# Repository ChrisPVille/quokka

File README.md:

# quokka
Quokka 6502 Microprocessor Trainer

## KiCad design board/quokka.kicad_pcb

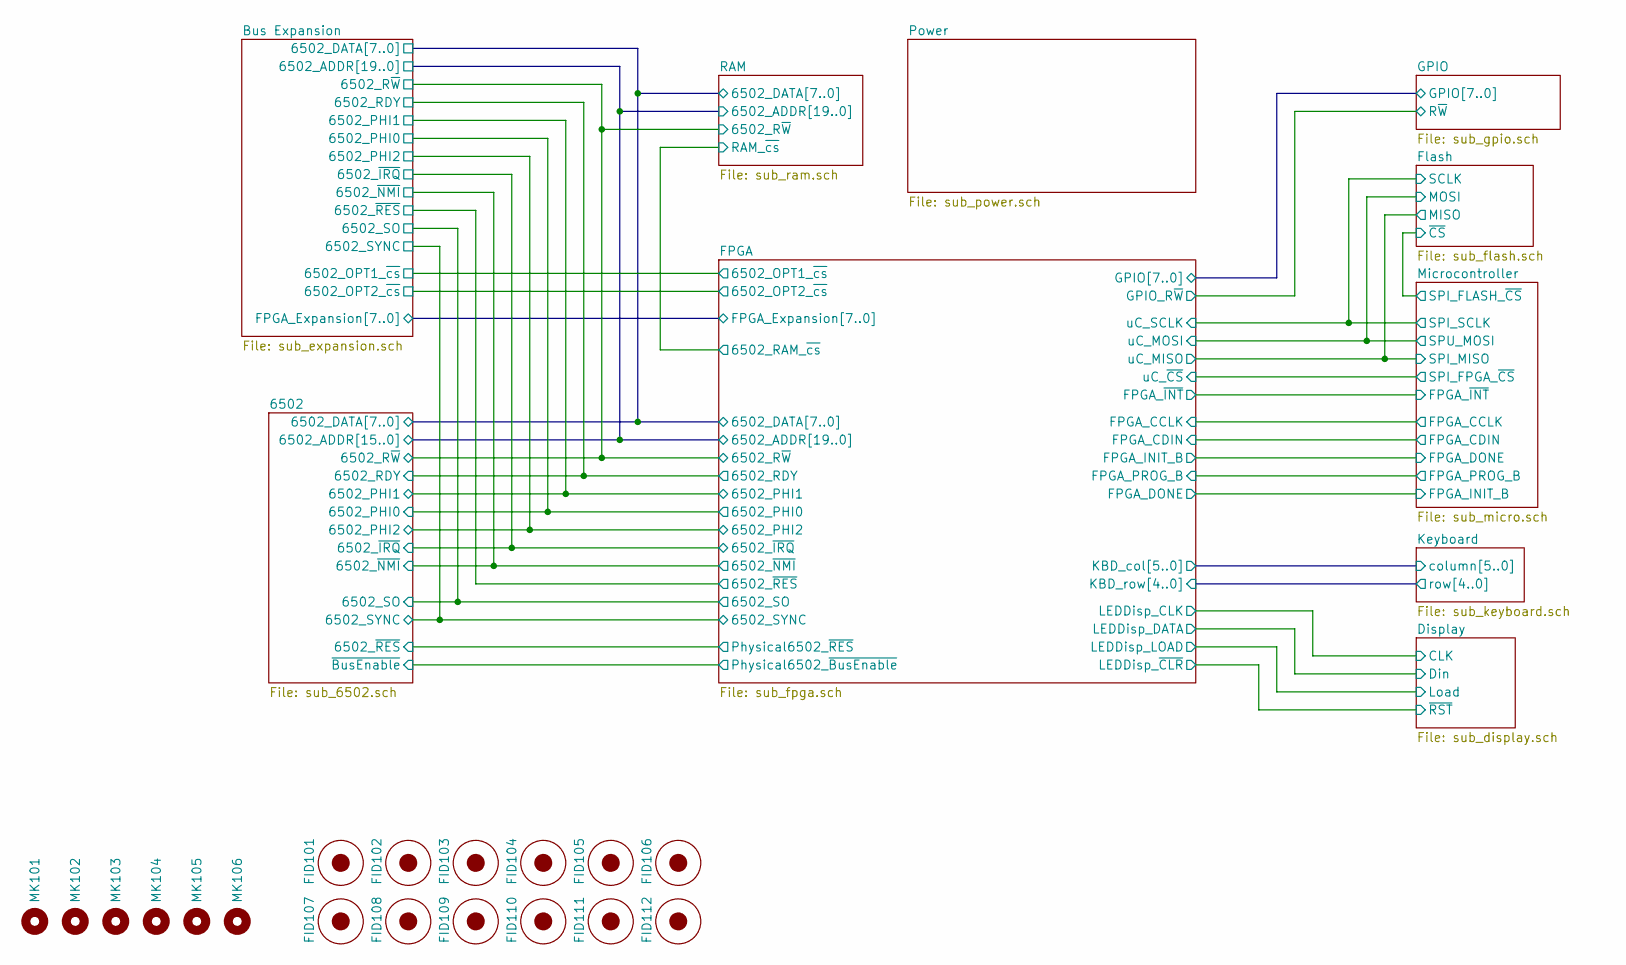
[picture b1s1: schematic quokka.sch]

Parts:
FID101, FID102, FID103, FID107, FID108, FID109, FID110, FID111, FID112: Fiducial; Fiducial_1mm_Dia_2.54mm_Outer_CopperTop
FID104, FID105, FID106: Fiducial; Fiducial_1mm_Dia_2.54mm_Outer_CopperBottom
MK101, MK102, MK103, MK104, MK105, MK106: Mounting_Hole; MountingHole_4.5mm

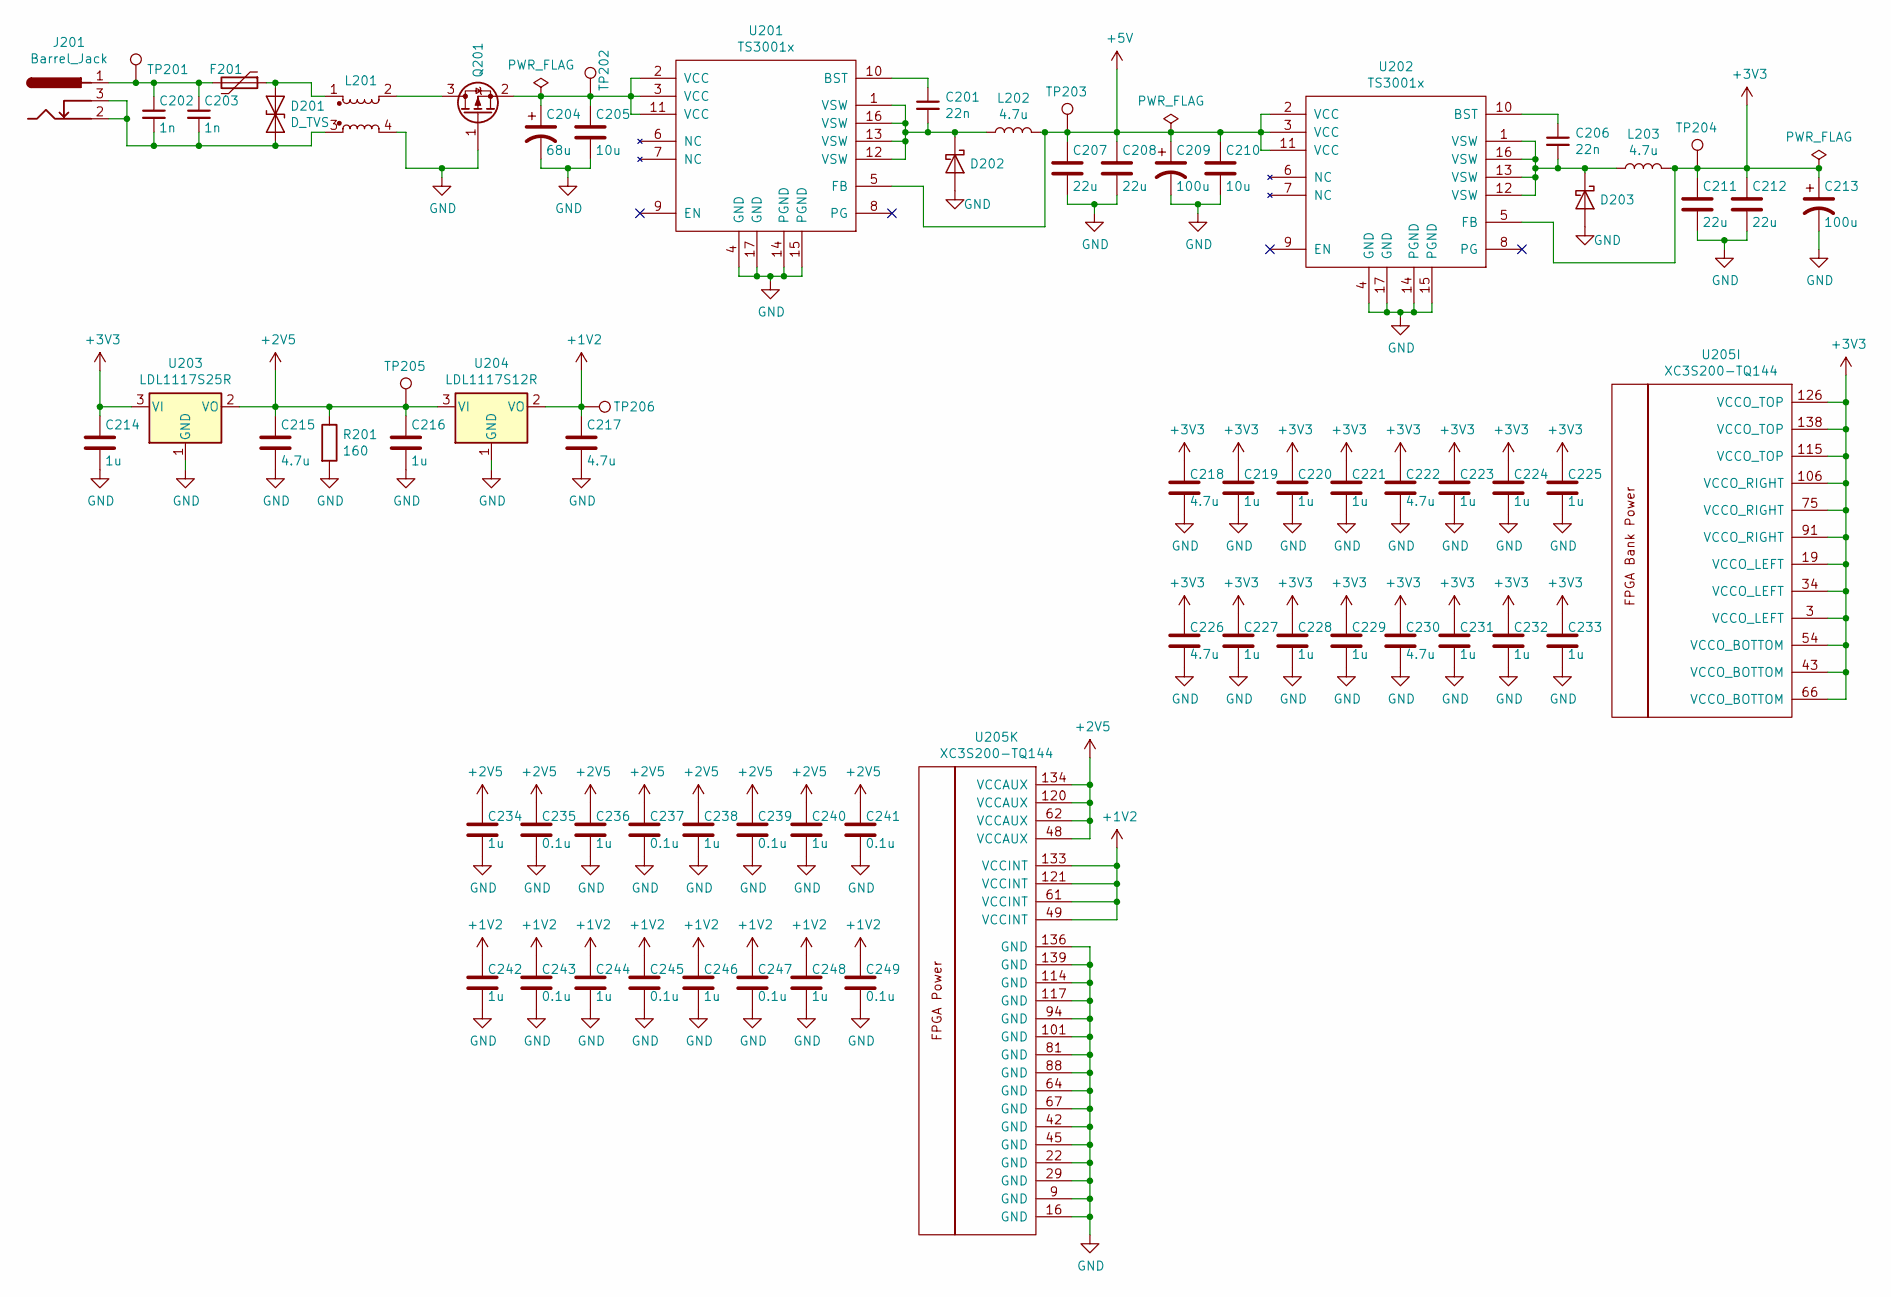
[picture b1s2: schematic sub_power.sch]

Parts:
C201, C206: 22n; C_0603_1608Metric
C202, C203: 1n; C_1206_3216Metric
C204: 68u; CP_Radial_D6.3mm_P2.50mm
C205, C210: 10u; C_1206_3216Metric
C207, C208, C211, C212: 22u; C_0805_2012Metric
C209, C213: 100u; CP_Radial_D8.0mm_P3.50mm
C214, C216, C219, C220, C221, C223, C224, C225, C227, C228, C229, C231, C232, C233, C234, C236, C238, C240, C242, C244, C246, C248: 1u; C_0603_1608Metric
C215, C217, C218, C222, C226, C230: 4.7u; C_0603_1608Metric
C235, C237, C239, C241, C243, C245, C247, C249: 0.1u; C_0603_1608Metric
D201: D_TVS; D_SMA
D202, D203: D_Schottky; D_SOD-123F
F201: Polyfuse; Fuse_2920_7451Metric
J201: Barrel_Jack; BarrelJack_CUI_PJ-102AH_Horizontal
L201: Power Choke; CM2021Y330R-10
L202, L203: 4.7u; L_Taiyo-Yuden_NR-60xx
Q201: Q_PMOS_GSD; SOT-23
R201: 160; R_1206_3216Metric
TP201, TP202, TP203, TP204, TP205, TP206: Test_Point; TestPoint_Pad_D1.5mm
U201, U202: TS3001x; UQFN-16-1EP_3x3mm_P0.5mm_EP1.75x1.75mm
U203: LDL1117S25R; SOT-223-3_TabPin2
U204: LDL1117S12R; SOT-223-3_TabPin2
U205: XC3S200-TQ144; LQFP-144_20x20mm_P0.5mm

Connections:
+1V2: C217.1, C242.1, C243.1, C244.1, C245.1, C246.1, C247.1, C248.1, C249.1, TP206.1, U204.2 (VO), U205.49 (VCCINT), U205.61 (VCCINT), U205.121 (VCCINT), U205.133 (VCCINT)
+2V5: C215.1, C216.1, C234.1, C235.1, C236.1, C237.1, C238.1, C239.1, C240.1, C241.1, R201.1, TP205.1, U203.2 (VO), U204.3 (VI), U205.48 (VCCAUX), U205.62 (VCCAUX), U205.120 (VCCAUX), U205.134 (VCCAUX); also elsewhere on the board
+5V: C207.1, C208.1, C209.1, C210.1, L202.2, TP203.1, U201.5 (FB), U202.2 (VCC), U202.3 (VCC), U202.11 (VCC); also elsewhere on the board
GND: C204.2, C205.2, C207.2, C208.2, C209.2, C210.2, C211.2, C212.2, C213.2, C214.2, C215.2, C216.2, C217.2, C218.2, C219.2, C220.2, C221.2, C222.2, C223.2, C224.2, C225.2, C226.2, C227.2, C228.2, C229.2, C230.2, C231.2, C232.2, C233.2, C234.2, C235.2, C236.2, C237.2, C238.2, C239.2, C240.2, C241.2, C242.2, C243.2, C244.2, C245.2, C246.2, C247.2, C248.2, C249.2, D202.2 (A), D203.2 (A), L201.4, Q201.1 (G), R201.2, U201.4 (GND), U201.14 (PGND), U201.15 (PGND), U201.17 (GND), U202.4 (GND), U202.14 (PGND), U202.15 (PGND), U202.17 (GND), U203.1 (GND), U204.1 (GND), U205.9 (GND), U205.16 (GND), U205.22 (GND), U205.29 (GND), U205.42 (GND), U205.45 (GND), U205.64 (GND), U205.67 (GND), U205.81 (GND), U205.88 (GND), U205.94 (GND), U205.101 (GND), U205.114 (GND), U205.117 (GND), U205.136 (GND), U205.139 (GND); also elsewhere on the board
unnamed: C201.1, U201.10 (BST)
unnamed: C201.2, D202.1 (K), L202.1, U201.1 (VSW), U201.12 (VSW), U201.13 (VSW), U201.16 (VSW)
unnamed: C202.1, C203.1, F201.2, J201.1, TP201.1
unnamed: C202.2, C203.2, D201.2 (A2), J201.2, J201.3, L201.3
unnamed: C204.1, C205.1, Q201.2 (S), TP202.1, U201.2 (VCC), U201.3 (VCC), U201.11 (VCC)
unnamed: C206.1, U202.10 (BST)
unnamed: C206.2, D203.1 (K), L203.1, U202.1 (VSW), U202.12 (VSW), U202.13 (VSW), U202.16 (VSW)
unnamed: D201.1 (A1), F201.1, L201.1
unnamed: L201.2, Q201.3 (D)

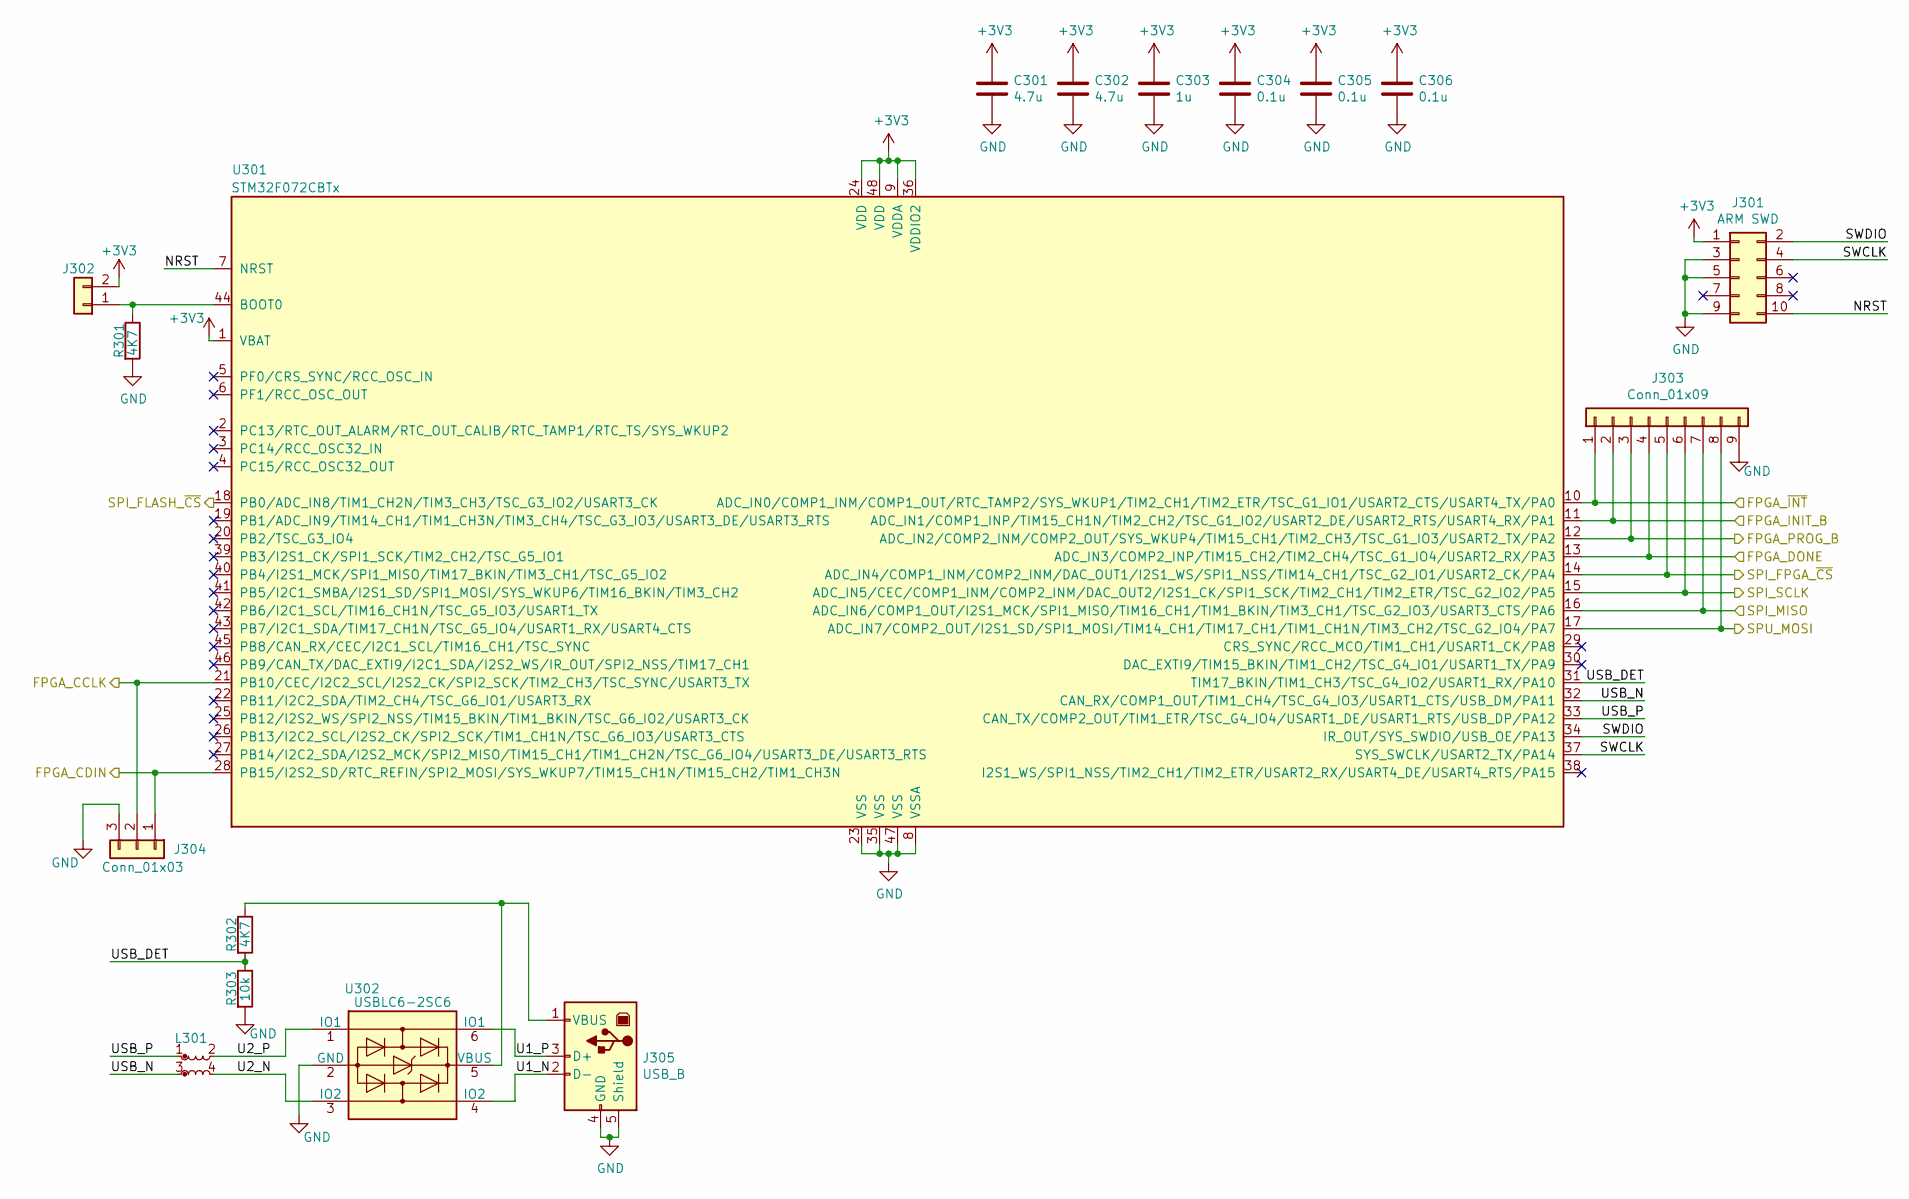
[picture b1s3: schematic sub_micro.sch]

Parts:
C301, C302: 4.7u; C_0603_1608Metric
C303: 1u; C_0603_1608Metric
C304, C305, C306: 0.1u; C_0603_1608Metric
J301: ARM SWD; PinHeader_2x05_P1.27mm_Vertical_SMD
J302: Conn_01x02; PinHeader_1x02_P2.54mm_Vertical
J303: Conn_01x09; PinHeader_1x09_P2.54mm_Vertical
J304: Conn_01x03; PinHeader_1x03_P2.54mm_Vertical
J305: USB_B; UE27BCX4
L301: USB Choke; DLW21H
R301, R302: 4K7; R_0603_1608Metric
R303: 10k; R_0603_1608Metric
U301: STM32F072CBTx; LQFP-48_7x7mm_P0.5mm
U302: USBLC6-2SC6; SOT-23-6

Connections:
/FPGA/FPGA_CCLK: J304.2, U301.21 (PB10/CEC/I2C2_SCL/I2S2_CK/SPI2_SCK/TIM2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); also elsewhere on the board
/FPGA/FPGA_CDIN: J304.1, U301.28 (PB15/I2S2_SD/RTC_REFIN/SPI2_MOSI/SYS_WK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); also elsewhere on the board
/FPGA/FPGA_DONE: J303.2, U301.11 (ADC_IN1/COMP1_INP/TIM15_CH1N/TIM2_CH2/T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); also elsewhere on the board
/FPGA/FPGA_PROG_B: J303.3, U301.12 (ADC_IN2/COMP2_INM/COMP2_OUT/SYS_WKUP4/T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); also elsewhere on the board
/FPGA/FPGA_~INT: J303.1, U301.10 (ADC_IN0/COMP1_INM/COMP1_OUT/RTC_TAMP2/S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); also elsewhere on the board
/Flash/MISO: J303.7, U301.16 (ADC_IN6/COMP1_OUT/I2S1_MCK/SPI1_MISO/TI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); also elsewhere on the board
/Flash/MOSI: J303.8, U301.17 (ADC_IN7/COMP2_OUT/I2S1_SD/SPI1_MOSI/TIM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); also elsewhere on the board
/Flash/SCLK: J303.6, U301.15 (ADC_IN5/CEC/COMP1_INM/COMP2_INM/DAC_OUT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); also elsewhere on the board
/Microcontroller/FPGA_DONE: J303.4, U301.13 (ADC_IN3/COMP2_INP/TIM15_CH2/TIM2_CH4/TS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); also elsewhere on the board
/Microcontroller/NRST: J301.10, U301.7 (NRST)
/Microcontroller/SPI_FLASH_~CS: U301.18 (PB0/ADC_IN8/TIM1_CH2N/TIM3_CH3/TSC_G3_I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); also elsewhere on the board
/Microcontroller/SPI_FPGA_~CS: J303.5, U301.14 (ADC_IN4/COMP1_INM/COMP2_INM/DAC_OUT1/I2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); also elsewhere on the board
/Microcontroller/SWCLK: J301.4, U301.37 (SYS_SWCLK/USART2_TX/PA14)
/Microcontroller/SWDIO: J301.2, U301.34 (IR_OUT/SYS_SWDIO/USB_OE/PA13)
/Microcontroller/U1_N: J305.2 (D-), U302.4 (IO2)
/Microcontroller/U1_P: J305.3 (D+), U302.6 (IO1)
/Microcontroller/U2_N: L301.4, U302.3 (IO2)
/Microcontroller/U2_P: L301.2, U302.1 (IO1)
/Microcontroller/USB_DET: R302.2, R303.1, U301.31 (TIM17_BKIN/TIM1_CH3/TSC_G4_IO2/USART1_R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)
/Microcontroller/USB_N: L301.3, U301.32 (CAN_RX/COMP1_OUT/TIM1_CH4/TSC_G4_IO3/US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)
/Microcontroller/USB_P: L301.1, U301.33 (CAN_TX/COMP2_OUT/TIM1_ETR/TSC_G4_IO4/US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)
GND: C301.2, C302.2, C303.2, C304.2, C305.2, C306.2, J301.3, J301.5, J301.9, J303.9, J304.3, J305.4 (GND), J305.5 (Shield), R301.2, R303.2, U301.8 (VSSA), U301.23 (VSS), U301.35 (VSS), U301.47 (VSS), U302.2 (GND); also elsewhere on the board
unnamed: J302.1, R301.1, U301.44 (BOOT0)
unnamed: J305.1 (VBUS), R302.1, U302.5 (VBUS)

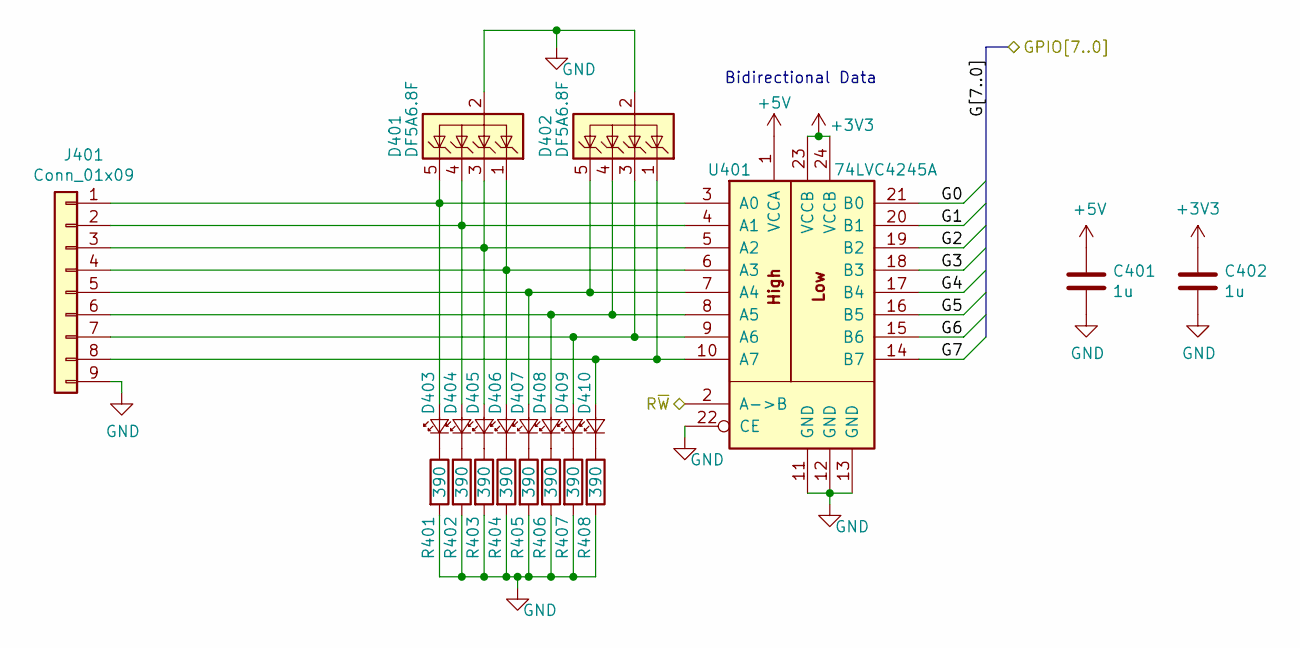
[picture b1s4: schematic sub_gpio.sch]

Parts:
C401, C402: 1u; C_0603_1608Metric
D401, D402: DF5A6.8F; SOT-353_SC-70-5
D403, D404, D405, D406, D407, D408, D409, D410: LED_Small; LED_0805_2012Metric
J401: Conn_01x09; PinHeader_1x09_P2.54mm_Vertical
R401, R402, R403, R404, R405, R406, R407, R408: 390; R_0603_1608Metric
U401: 74LVC4245A; TSSOP-24_4.4x7.8mm_P0.65mm

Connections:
+5V: C401.1, U401.1 (VCCA); also elsewhere on the board
/FPGA/G0: U401.21 (B0); also elsewhere on the board
/FPGA/G1: U401.20 (B1); also elsewhere on the board
/FPGA/G2: U401.19 (B2); also elsewhere on the board
/FPGA/G3: U401.18 (B3); also elsewhere on the board
/FPGA/G4: U401.17 (B4); also elsewhere on the board
/FPGA/G5: U401.16 (B5); also elsewhere on the board
/FPGA/G6: U401.15 (B6); also elsewhere on the board
/FPGA/G7: U401.14 (B7); also elsewhere on the board
/FPGA/GPIO_R~W: U401.2 (A->B); also elsewhere on the board
GND: C401.2, C402.2, D401.2 (A), D402.2 (A), J401.9, R401.2, R402.2, R403.2, R404.2, R405.2, R406.2, R407.2, R408.2, U401.11 (GND), U401.12 (GND), U401.13 (GND), U401.22 (CE); also elsewhere on the board
unnamed: D401.1 (K), D406.2 (A), J401.4, U401.6 (A3)
unnamed: D401.3 (K), D405.2 (A), J401.3, U401.5 (A2)
unnamed: D401.4 (K), D404.2 (A), J401.2, U401.4 (A1)
unnamed: D401.5 (K), D403.2 (A), J401.1, U401.3 (A0)
unnamed: D402.1 (K), D410.2 (A), J401.8, U401.10 (A7)
unnamed: D402.3 (K), D409.2 (A), J401.7, U401.9 (A6)
unnamed: D402.4 (K), D408.2 (A), J401.6, U401.8 (A5)
unnamed: D402.5 (K), D407.2 (A), J401.5, U401.7 (A4)
unnamed: D403.1 (K), R401.1
unnamed: D404.1 (K), R402.1
unnamed: D405.1 (K), R403.1
unnamed: D406.1 (K), R404.1
unnamed: D407.1 (K), R405.1
unnamed: D408.1 (K), R406.1
unnamed: D409.1 (K), R407.1
unnamed: D410.1 (K), R408.1

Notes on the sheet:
Bidirectional Data

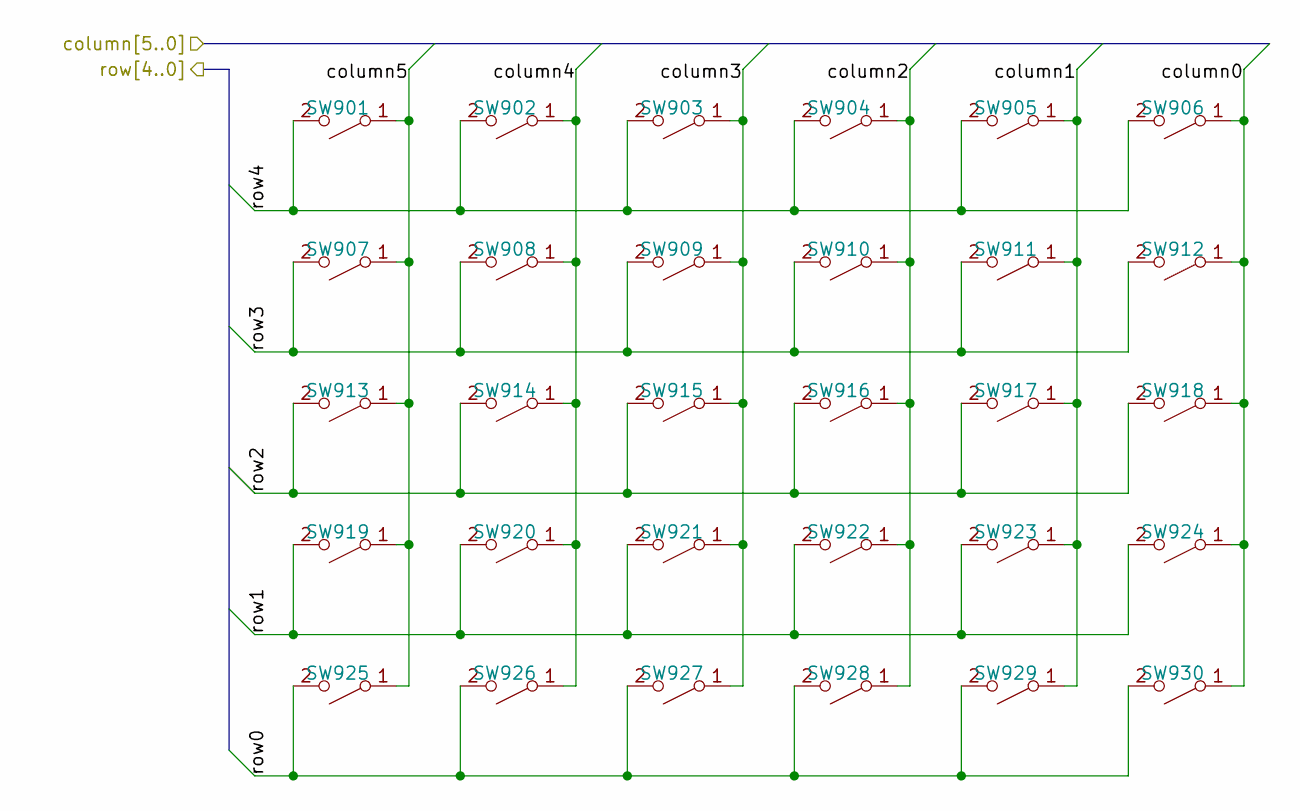
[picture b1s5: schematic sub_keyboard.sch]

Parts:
SW901, SW902, SW903, SW904, SW905, SW906, SW907, SW908, SW909, SW910, SW911, SW912, SW913, SW914, SW915, SW916, SW917, SW918, SW919, SW920, SW921, SW922, SW923, SW924, SW925, SW926, SW927, SW928, SW929, SW930: SW_SPST; SW_Cherry_MX1A_1.00u_PCB

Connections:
/FPGA/C0: SW906.1 (A), SW912.1 (A), SW918.1 (A), SW924.1 (A), SW930.1 (A); also elsewhere on the board
/FPGA/C1: SW905.1 (A), SW911.1 (A), SW917.1 (A), SW923.1 (A), SW929.1 (A); also elsewhere on the board
/FPGA/C2: SW904.1 (A), SW910.1 (A), SW916.1 (A), SW922.1 (A), SW928.1 (A); also elsewhere on the board
/FPGA/C3: SW903.1 (A), SW909.1 (A), SW915.1 (A), SW921.1 (A), SW927.1 (A); also elsewhere on the board
/FPGA/C4: SW902.1 (A), SW908.1 (A), SW914.1 (A), SW920.1 (A), SW926.1 (A); also elsewhere on the board
/FPGA/C5: SW901.1 (A), SW907.1 (A), SW913.1 (A), SW919.1 (A), SW925.1 (A); also elsewhere on the board
/FPGA/R0: SW925.2 (B), SW926.2 (B), SW927.2 (B), SW928.2 (B), SW929.2 (B), SW930.2 (B); also elsewhere on the board
/FPGA/R1: SW919.2 (B), SW920.2 (B), SW921.2 (B), SW922.2 (B), SW923.2 (B), SW924.2 (B); also elsewhere on the board
/FPGA/R2: SW913.2 (B), SW914.2 (B), SW915.2 (B), SW916.2 (B), SW917.2 (B), SW918.2 (B); also elsewhere on the board
/FPGA/R3: SW907.2 (B), SW908.2 (B), SW909.2 (B), SW910.2 (B), SW911.2 (B), SW912.2 (B); also elsewhere on the board
/FPGA/R4: SW901.2 (B), SW902.2 (B), SW903.2 (B), SW904.2 (B), SW905.2 (B), SW906.2 (B); also elsewhere on the board

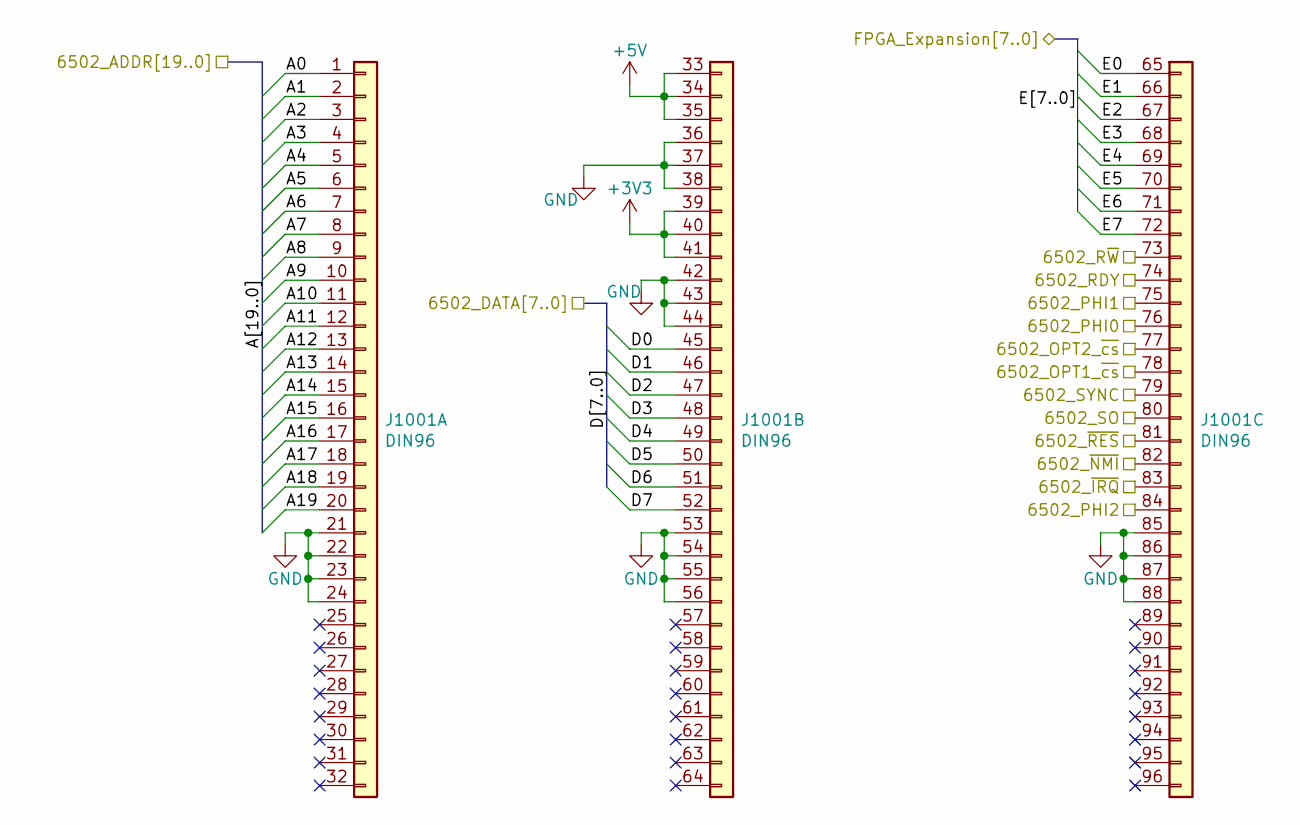
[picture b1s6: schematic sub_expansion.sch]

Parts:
J1001: DIN96; DIN-8609-2030

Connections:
+5V: J1001.33 (Pin_1), J1001.34 (Pin_2), J1001.35 (Pin_3); also elsewhere on the board
/6502/6502_PHI0: J1001.76 (Pin_12); also elsewhere on the board
/6502/6502_PHI1: J1001.75 (Pin_11); also elsewhere on the board
/6502/6502_PHI2: J1001.84 (Pin_20); also elsewhere on the board
/6502/6502_RDY: J1001.74 (Pin_10); also elsewhere on the board
/6502/6502_R~W: J1001.73 (Pin_9); also elsewhere on the board
/6502/6502_SO: J1001.80 (Pin_16); also elsewhere on the board
/6502/6502_SYNC: J1001.79 (Pin_15); also elsewhere on the board
/6502/6502_~IRQ: J1001.83 (Pin_19); also elsewhere on the board
/6502/6502_~NMI: J1001.82 (Pin_18); also elsewhere on the board
/6502/B_D0: J1001.45 (Pin_13); also elsewhere on the board
/6502/B_D1: J1001.46 (Pin_14); also elsewhere on the board
/6502/B_D2: J1001.47 (Pin_15); also elsewhere on the board
/6502/B_D3: J1001.48 (Pin_16); also elsewhere on the board
/6502/B_D4: J1001.49 (Pin_17); also elsewhere on the board
/6502/B_D5: J1001.50 (Pin_18); also elsewhere on the board
/6502/B_D6: J1001.51 (Pin_19); also elsewhere on the board
/6502/B_D7: J1001.52 (Pin_20); also elsewhere on the board
/Bus Expansion/6502_OPT1_~cs: J1001.78 (Pin_14); also elsewhere on the board
/Bus Expansion/6502_OPT2_~cs: J1001.77 (Pin_13); also elsewhere on the board
/Bus Expansion/6502_~RES: J1001.81 (Pin_17); also elsewhere on the board
/Bus Expansion/A0: J1001.1; also elsewhere on the board
/Bus Expansion/A1: J1001.2; also elsewhere on the board
/Bus Expansion/A2: J1001.3; also elsewhere on the board
/Bus Expansion/A3: J1001.4; also elsewhere on the board
/Bus Expansion/A4: J1001.5; also elsewhere on the board
/Bus Expansion/A5: J1001.6; also elsewhere on the board
/Bus Expansion/A6: J1001.7; also elsewhere on the board
/Bus Expansion/A7: J1001.8; also elsewhere on the board
/Bus Expansion/A8: J1001.9; also elsewhere on the board
/Bus Expansion/A9: J1001.10; also elsewhere on the board
/Bus Expansion/A10: J1001.11; also elsewhere on the board
/Bus Expansion/A11: J1001.12; also elsewhere on the board
/Bus Expansion/A12: J1001.13; also elsewhere on the board
/Bus Expansion/A13: J1001.14; also elsewhere on the board
/Bus Expansion/A14: J1001.15; also elsewhere on the board
/Bus Expansion/A15: J1001.16; also elsewhere on the board
/Bus Expansion/A16: J1001.17; also elsewhere on the board
/Bus Expansion/A17: J1001.18; also elsewhere on the board
/Bus Expansion/A18: J1001.19; also elsewhere on the board
/Bus Expansion/A19: J1001.20; also elsewhere on the board
/Bus Expansion/E0: J1001.65 (Pin_1); also elsewhere on the board
/Bus Expansion/E1: J1001.66 (Pin_2); also elsewhere on the board
/Bus Expansion/E2: J1001.67 (Pin_3); also elsewhere on the board
/Bus Expansion/E3: J1001.68 (Pin_4); also elsewhere on the board
/Bus Expansion/E4: J1001.69 (Pin_5); also elsewhere on the board
/Bus Expansion/E5: J1001.70 (Pin_6); also elsewhere on the board
/Bus Expansion/E6: J1001.71 (Pin_7); also elsewhere on the board
/Bus Expansion/E7: J1001.72 (Pin_8); also elsewhere on the board
GND: J1001.21, J1001.22, J1001.23, J1001.24, J1001.36 (Pin_4), J1001.37 (Pin_5), J1001.38 (Pin_6), J1001.42 (Pin_10), J1001.43 (Pin_11), J1001.44 (Pin_12), J1001.53 (Pin_21), J1001.54 (Pin_22), J1001.55 (Pin_23), J1001.56 (Pin_24), J1001.85 (Pin_21), J1001.86 (Pin_22), J1001.87 (Pin_23), J1001.88 (Pin_24); also elsewhere on the board

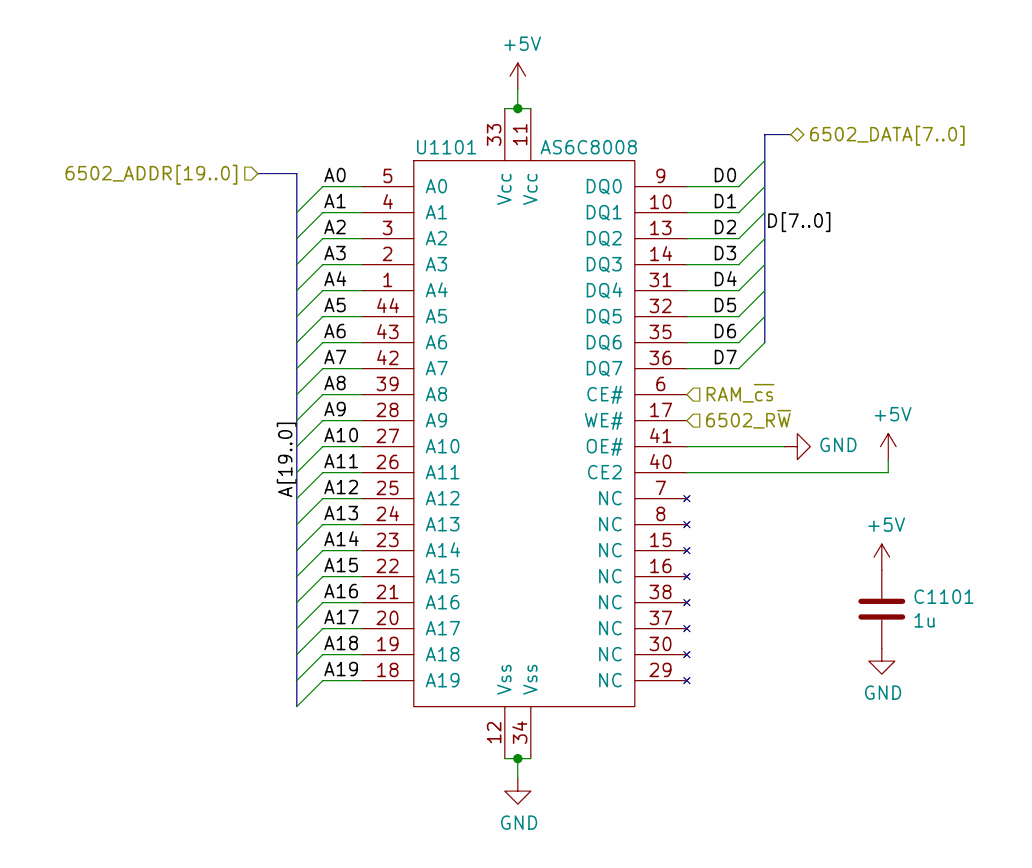
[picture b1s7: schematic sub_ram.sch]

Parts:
C1101: 1u; C_0603_1608Metric
U1101: AS6C8008; AS6C8008-SOIC-44

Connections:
+5V: C1101.1, U1101.11 (Vcc), U1101.33 (Vcc), U1101.40 (CE2); also elsewhere on the board
/6502/6502_R~W: U1101.17 (WE#); also elsewhere on the board
/6502/B_D0: U1101.9 (DQ0); also elsewhere on the board
/6502/B_D1: U1101.10 (DQ1); also elsewhere on the board
/6502/B_D2: U1101.13 (DQ2); also elsewhere on the board
/6502/B_D3: U1101.14 (DQ3); also elsewhere on the board
/6502/B_D4: U1101.31 (DQ4); also elsewhere on the board
/6502/B_D5: U1101.32 (DQ5); also elsewhere on the board
/6502/B_D6: U1101.35 (DQ6); also elsewhere on the board
/6502/B_D7: U1101.36 (DQ7); also elsewhere on the board
/Bus Expansion/A0: U1101.5 (A0); also elsewhere on the board
/Bus Expansion/A1: U1101.4 (A1); also elsewhere on the board
/Bus Expansion/A2: U1101.3 (A2); also elsewhere on the board
/Bus Expansion/A3: U1101.2 (A3); also elsewhere on the board
/Bus Expansion/A4: U1101.1 (A4); also elsewhere on the board
/Bus Expansion/A5: U1101.44 (A5); also elsewhere on the board
/Bus Expansion/A6: U1101.43 (A6); also elsewhere on the board
/Bus Expansion/A7: U1101.42 (A7); also elsewhere on the board
/Bus Expansion/A8: U1101.39 (A8); also elsewhere on the board
/Bus Expansion/A9: U1101.28 (A9); also elsewhere on the board
/Bus Expansion/A10: U1101.27 (A10); also elsewhere on the board
/Bus Expansion/A11: U1101.26 (A11); also elsewhere on the board
/Bus Expansion/A12: U1101.25 (A12); also elsewhere on the board
/Bus Expansion/A13: U1101.24 (A13); also elsewhere on the board
/Bus Expansion/A14: U1101.23 (A14); also elsewhere on the board
/Bus Expansion/A15: U1101.22 (A15); also elsewhere on the board
/Bus Expansion/A16: U1101.21 (A16); also elsewhere on the board
/Bus Expansion/A17: U1101.20 (A17); also elsewhere on the board
/Bus Expansion/A18: U1101.19 (A18); also elsewhere on the board
/Bus Expansion/A19: U1101.18 (A19); also elsewhere on the board
/FPGA/6502_RAM_~cs: U1101.6 (CE#); also elsewhere on the board
GND: C1101.2, U1101.12 (Vss), U1101.34 (Vss), U1101.41 (OE#); also elsewhere on the board

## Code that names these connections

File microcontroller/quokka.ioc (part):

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Mcu.Name=STM32F072C(8-B)Tx
Mcu.Package=LQFP48
Mcu.UserName=STM32F072CBTx
PA0.Signal=GPIO_Input
PA1.Signal=GPIO_Input
PA11.Mode=Device
PA11.Signal=USB_DM
PA12.Mode=Device
PA12.Signal=USB_DP
PA13.Mode=Serial_Wire
PA13.Signal=SYS_SWDIO
PA14.Mode=Serial_Wire
PA14.Signal=SYS_SWCLK
PA2.Signal=GPIO_Output
PA3.Signal=GPIO_Input
PA4.Mode=NSS_Signal_Hard_Output
PA4.Signal=SPI1_NSS
PA5.Mode=Full_Duplex_Master
PA5.Signal=SPI1_SCK
PA6.Mode=Full_Duplex_Master
PA6.Signal=SPI1_MISO
PA7.Mode=Full_Duplex_Master
PA7.Signal=SPI1_MOSI
PB0.Signal=GPIO_Output
PB10.GPIOParameters=GPIO_PuPd
PB10.GPIO_PuPd=GPIO_NOPULL
PB10.Mode=TX_Only_Simplex_Unidirect_Master
PB10.Signal=SPI2_SCK
PB15.Mode=TX_Only_Simplex_Unidirect_Master
PB15.Signal=SPI2_MOSI
RCC.SYSCLKFreq_VALUE=48000000
RCC.SYSCLKSource=RCC_SYSCLKSOURCE_HSI48

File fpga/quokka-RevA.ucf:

NET "RAW25MHZ" LOC = P53 | IOSTANDARD = LVCMOS33 | TNM_NET = "RAW25MHZ";
TIMESPEC TS_RAW25MHZ = PERIOD "RAW25MHZ" 25 MHz HIGH 50 % INPUT_JITTER 5 ps;

NET "G[7]" LOC = P52 | IOSTANDARD = LVCMOS33;
NET "G[6]" LOC = P51 | IOSTANDARD = LVCMOS33;
NET "G[5]" LOC = P50 | IOSTANDARD = LVCMOS33;
NET "G[4]" LOC = P47 | IOSTANDARD = LVCMOS33;
NET "G[3]" LOC = P46 | IOSTANDARD = LVCMOS33;
NET "G[2]" LOC = P44 | IOSTANDARD = LVCMOS33;
NET "G[1]" LOC = P41 | IOSTANDARD = LVCMOS33;
NET "G[0]" LOC = P40 | IOSTANDARD = LVCMOS33;
NET "GPIO_RW" LOC = P55 | IOSTANDARD = LVCMOS33;

NET "LCD_CLK" LOC = P124 | IOSTANDARD = LVCMOS33;
NET "LCD_DATA" LOC = P122 | IOSTANDARD = LVCMOS33;
NET "LCD_LOAD" LOC = P119 | IOSTANDARD = LVCMOS33;
NET "LCD_CLR" LOC = P1 | IOSTANDARD = LVCMOS33;

NET "PHI1" LOC = P127 | IOSTANDARD = LVCMOS33;
NET "PHI2" LOC = P128 | IOSTANDARD = LVCMOS33;
NET "SYNC" LOC = P129 | IOSTANDARD = LVCMOS33;
NET "IRQ" LOC = P130 | IOSTANDARD = LVCMOS33;
NET "RDY" LOC = P131 | IOSTANDARD = LVCMOS33;
NET "NMIn" LOC = P132 | IOSTANDARD = LVCMOS33;
NET "phys6502_RESn" LOC = P135 | IOSTANDARD = LVCMOS33;
NET "RES" LOC = P137 | IOSTANDARD = LVCMOS33;
NET "SO" LOC = P140 | IOSTANDARD = LVCMOS33;
NET "phys6502_BusEnableN" LOC = P141 | IOSTANDARD = LVCMOS33;
NET "RAM_csN" LOC = P112 | IOSTANDARD = LVCMOS33;
NET "OPT1_csN" LOC = P113 | IOSTANDARD = LVCMOS33;
NET "OPT2_csN" LOC = P118 | IOSTANDARD = LVCMOS33;
NET "RW" LOC = P123 | IOSTANDARD = LVCMOS33;
NET "PHI0" LOC = P125 | IOSTANDARD = LVCMOS33;
NET "EnableXceversN" LOC = P2 | IOSTANDARD = LVCMOS33;
NET "DataDir" LOC = P4 | IOSTANDARD = LVCMOS33;
NET "Drive6502BusN" LOC = P5 | IOSTANDARD = LVCMOS33;
NET "SenseRES" LOC = P6 | IOSTANDARD = LVCMOS33;

NET "D[0]" LOC = P73 | IOSTANDARD = LVCMOS33;
NET "D[1]" LOC = P74 | IOSTANDARD = LVCMOS33;
NET "D[2]" LOC = P76 | IOSTANDARD = LVCMOS33;
NET "D[3]" LOC = P77 | IOSTANDARD = LVCMOS33;
NET "D[4]" LOC = P78 | IOSTANDARD = LVCMOS33;
NET "D[5]" LOC = P79 | IOSTANDARD = LVCMOS33;
NET "D[6]" LOC = P80 | IOSTANDARD = LVCMOS33;
NET "D[7]" LOC = P82 | IOSTANDARD = LVCMOS33;

NET "A[0]" LOC = P108 | IOSTANDARD = LVCMOS33;
NET "A[1]" LOC = P107 | IOSTANDARD = LVCMOS33;
NET "A[2]" LOC = P105 | IOSTANDARD = LVCMOS33;
NET "A[3]" LOC = P104 | IOSTANDARD = LVCMOS33;
NET "A[4]" LOC = P103 | IOSTANDARD = LVCMOS33;
NET "A[5]" LOC = P102 | IOSTANDARD = LVCMOS33;
NET "A[6]" LOC = P100 | IOSTANDARD = LVCMOS33;
NET "A[7]" LOC = P99 | IOSTANDARD = LVCMOS33;
NET "A[8]" LOC = P98 | IOSTANDARD = LVCMOS33;
NET "A[9]" LOC = P97 | IOSTANDARD = LVCMOS33;
NET "A[10]" LOC = P96 | IOSTANDARD = LVCMOS33;
NET "A[11]" LOC = P95 | IOSTANDARD = LVCMOS33;
NET "A[12]" LOC = P93 | IOSTANDARD = LVCMOS33;
NET "A[13]" LOC = P92 | IOSTANDARD = LVCMOS33;
NET "A[14]" LOC = P90 | IOSTANDARD = LVCMOS33;
NET "A[15]" LOC = P89 | IOSTANDARD = LVCMOS33;
NET "Ahigh[16]" LOC = P84 | IOSTANDARD = LVCMOS33;
NET "Ahigh[17]" LOC = P85 | IOSTANDARD = LVCMOS33;
NET "Ahigh[18]" LOC = P86 | IOSTANDARD = LVCMOS33;
NET "Ahigh[19]" LOC = P87 | IOSTANDARD = LVCMOS33;

NET "KBD_row[0]" LOC = P20 | IOSTANDARD = LVCMOS33;
NET "KBD_row[1]" LOC = P21 | IOSTANDARD = LVCMOS33;
NET "KBD_row[2]" LOC = P23 | IOSTANDARD = LVCMOS33;
NET "KBD_row[3]" LOC = P24 | IOSTANDARD = LVCMOS33;
NET "KBD_row[4]" LOC = P25 | IOSTANDARD = LVCMOS33;
NET "KBD_col[0]" LOC = P12 | IOSTANDARD = LVCMOS33 | PULLDOWN;
NET "KBD_col[1]" LOC = P13 | IOSTANDARD = LVCMOS33 | PULLDOWN;
NET "KBD_col[2]" LOC = P14 | IOSTANDARD = LVCMOS33 | PULLDOWN;
NET "KBD_col[3]" LOC = P15 | IOSTANDARD = LVCMOS33 | PULLDOWN;
NET "KBD_col[4]" LOC = P17 | IOSTANDARD = LVCMOS33 | PULLDOWN;
NET "KBD_col[5]" LOC = P18 | IOSTANDARD = LVCMOS33 | PULLDOWN;

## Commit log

2018-03-03 Added skeleton schematic
2018-03-03 gitignore for FPGA files
2018-03-03 Added empty fpga project
2018-03-04 Added microcontroller STM32CubeMX definition
2018-03-04 Moved to KiCad 5
2018-03-06 Switched to crystal-less part
2018-03-06 Added some buttons
2018-03-07 Updated keyboard
2018-03-09 Got that irritating FPGA footprint done
2018-03-10 More progress on the schematic. 6502 Done.
2018-03-10 More schematic progress
2018-03-12 Level converters complete, display almost done
2018-03-15 Bus signal connectivity rebuilt
2018-03-16 gpio done
2018-03-17 RAM Done
2018-03-17 made some changes based on projected power budget
2018-03-17 Schematics mostly complete
2018-03-18 Started picking footprints. Merged many components.
2018-03-18 More footprints done. Went with simpler test-pads.
2018-03-18 Fixed swapped pin and some labels
2018-03-18 Added SPI Flash for uC
2018-03-18 Most footprints associated
2018-03-18 Almost all footprints done
2018-03-19 All footprints done
2018-03-19 Started on board
2018-03-21 more progress on board
2018-03-21 Power supply routed
2018-03-22 Most critical nets routed
2018-03-22 Ready for autorouting
2018-03-22 All nets routed
2018-03-22 Renamed SPI flash schematic file
2018-03-22 Cleaned up DRC violations
2018-03-22 Cleaned up silkscreen designators
2018-03-23 Added fids, made PDF
2018-03-23 Resolved accidental DRC error
2018-03-23 Generated RevA gerbers
2018-03-23 Ignore temporary zip files
2018-04-09 Planning some changes for revB
2018-04-09 Added constraints file
2018-04-09 Turned all the digits on
2018-04-10 Added some test modules for the display
2018-04-11 Added hex->SR output mapping
2018-04-12 Abstracted some of the display code
2018-04-15 Added working display driver
2018-04-15 Fixed swapped digits
2018-04-22 Added keyboard driver to repo, activated pulldowns on matrix input lines to fix ghost presses caused by capacitive coupling
2018-04-30 Added simple CPU control
2018-04-30 Added clock IP block
2018-05-05 Added cc65 for assembly monitor program
2018-05-05 Updated software
2018-05-05 Added discrete LED mapping and abstracted some magic numbers
2018-05-05 Added ability to display some data from the 6502 on interrupt
2018-05-05 First pass at monitor reading all internal registers
2018-05-05 Mapped SR to leds
2018-05-05 It would be helpful if the literals were marked as such
2018-05-05 Improved chip-selects
2018-05-05 Reduced discrete LED duty cycle as they were significantly brighter than the 14-segs
2018-05-05 Reworked run/halt arch to allow eventual single stepping
2018-05-05 Single stepping mostly working
2018-05-05 Should only wait for 2 instruction after ready from processor
2018-05-06 Added step through reset ability
2018-05-06 Added ability for modification of all registers except SP
2018-05-06 Added support for FPGA assisted indirect addressing
2018-05-06 Fixed image size
2018-05-06 First stab at load/store in FPGA
2018-05-06 Added shell of UI control
2018-05-06 Spelling would be nice
2018-05-06 Added simple UI control
2018-05-06 Fixed UI SR
2018-05-06 Fixed some implicit wires
2018-05-06 Again, picking the correct reg is helpful
2018-05-06 Rearranged the load/store logic
2018-05-06 Swap conditions
2018-05-06 Switched to positive acknowledgment system
2018-05-06 Restored X, added auto-clear to ui
2018-05-06 Well, BIT didn't work the way I thought it did
2018-05-06 First pass at an address preference mode for load/store operations on the UI
2018-05-06 Some progress on auto-increment
2018-05-06 Put autoincrement aside for now while the UX is figured out
2018-05-07 Re-added a simple autoincrement mode to make sequential stores easier
2023-07-03 Added board image
